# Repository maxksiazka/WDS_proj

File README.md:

# Wizualizacja kokpitu samolotu 

## O projekcie
Projekt polega na zaprojektowaniu i implementacji aplikacji graficznej mimikującej nowoczesny "szklany kokpit" samolotu.

## Warstwa sprzętowa (Embedded i Czujniki)
Projekt obejmuje warstwę embedded, w której centralną funkcję pełni mikrokontroler **Raspberry Pi Pico 2W**. Do mikrokontrolera podłączony jest zestaw następujących układów pomiarowych:
* **Moduł inercyjny (IMU 10-DoF)** - zawierający akcelerometr, żyroskop, magnetometr oraz barometr statyczny. - *modGY-86*:
  * **Akcelerometr i żyroskop**: Służą do wyznaczania sztucznego horyzontu (ang. *attitude indicator*).
  * **Magnetometr**: Umożliwia sterowanie wirtualnym kompasem (ang. *heading indicator*) oraz orientowanie wskaźnika kursu.
  * **Barometr statyczny**: Służy do przeliczania spadku ciśnienia w celu określenia wysokości lotu oraz uzyskania prędkości pionowej, pełniąc funkcję wariometru.
* **System pomiaru ciśnienia różnicowego** - *Hx-710B*: Działa jako prędkościomierz ciśnieniowy, mający na celu uzyskanie prędkości przyrządowej statku powietrznego (ang. *indicated airspeed* - IAS).
* **Moduł GPS** - *NEO-M8N*: Wykorzystywany do reprezentacji prędkości nad ziemią (ang. *ground speed* - GS) oraz rzeczywistego kąta ścieżki (ang. *course over ground* - COG).

## Architektura oprogramowania
* Architektura systemu opiera się na ciągłej akwizycji wartości z wymienionych układów pomiarowych, ich wstępnym przetwarzaniu na poziomie mikrokontrolera oraz strumieniowaniu do komputera PC.
* Algorytmy te integrują surowe odczyty, tworząc spójny, odporny na zakłócenia i responsywny interfejs łączący funkcjonalności ekranów PFD (ang. *Primary Flight Display*) oraz MFD (ang. *Multi-Function Display*).
* Intefejs będzie osobną aplikacją desktopową, która będzie odbierać dane z mikrokontrolera i wizualizować je w czasie rzeczywistym za pomocą biblioteki graficznej Qt6.

## Specyfikacja finalnego produktu
* Finalnym produktem jest zintegrowany system pomiarowo-wizualizacyjny, który ma na celu imitację samolotu.
* Część sprzętowa, mająca formę fizycznej makiety, pełni funkcję uproszczonego układu AHRS (ang. *Attitude and Heading Reference System*) zintegrowanego z czujnikiem ciśnienia różnicowego (pomiar prędkości przyrządowej) oraz odbiornikiem GPS.
* Zbierane dane są strumieniowane do aplikacji na komputerze PC, która realizuje funkcje interfejsów PFD oraz MFD.
* Gotowa aplikacja bezpośrednio reaguje na zmiany położenia makiety oraz zmiany środowiskowe. **Data**: 20 marca 2026.

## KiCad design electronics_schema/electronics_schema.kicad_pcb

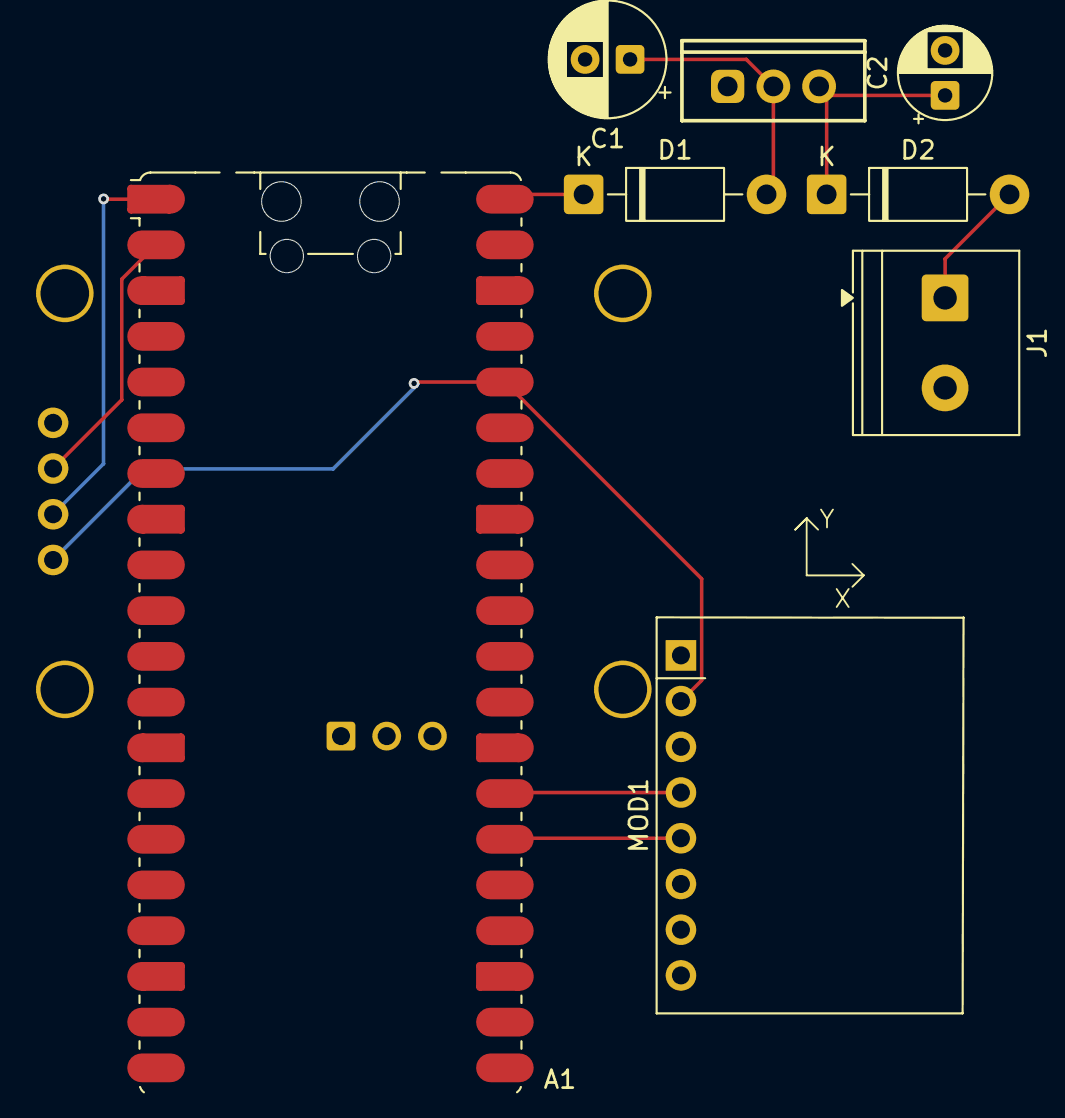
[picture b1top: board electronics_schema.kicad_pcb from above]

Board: 2 copper layers, 9 parts (1 on the bottom side), 10 nets.

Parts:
A1: RaspberryPi_Pico_W; RaspberryPi_Pico_W_SMD_HandSolder
C1: 100u; CP_Radial_D6.3mm_P2.50mm
C2: 10u; CP_Radial_D5.0mm_P2.50mm
D1, D2: 1N5819; D_DO-41_SOD81_P10.16mm_Horizontal
J1: Screw_Terminal_2_P5.00mm; TerminalBlock_Phoenix_PT-1,5-2-5.0-H_1x02_P5.00mm_Horizontal
MOD1: modGY-87
MOD2: GY-GPS6MV2
U1: LM1117T-5.0; TO-220-3

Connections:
3v3: A1.36 (3V3), MOD1.2 (3.3V), MOD2.1 (VCC)
/gps_RX: A1.1 (GPIO0), MOD2.2 (RX)
/gps_TX: A1.2 (GPIO1), MOD2.3 (TX)
/imu_SCL: A1.27 (GPIO21), MOD1.4 (SCL)
/imu_SDA: A1.26 (GPIO20), MOD1.5 (SDA)
GND: A1.3 (GND), A1.8 (GND), A1.13 (GND), A1.18 (GND), A1.23 (GND), A1.28 (GND), A1.38 (GND), C1.2, C2.2, J1.2, MOD1.3 (GND), MOD2.4 (GND), U1.1 (GND)
unnamed: A1.40 (VBUS), D1.1 (K)
unnamed: C1.1, D1.2 (A), U1.2 (VO)
unnamed: C2.1, D2.1 (K), U1.3 (VI)
VBATT: D2.2 (A), J1.1

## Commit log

2026-03-21 feat(project): Added project description to README.md, created TASKS.md with approximate to-do list
2026-03-21 feat(hardware): Created a template Pico 2W project
2026-03-21 feat(hardware): added simple hello world, gitignore
2026-03-21 feat(hardware): wrote UDP IPv4 address discovery code
2026-03-21 feat(hardware): added legacy TCP code from maxksiazka/SR_Project, needs adaptation
2026-03-23 feat(hardware): finished udp discovery protocol, changed lwip callbacks to static
2026-03-24 feat(qt): Created a simple TCP server QtCoreApplication, with UDP IP Address broadcasting.
    The application is very barebones for now, for now its purpose is to
    verify the link between the server and MCU.
    Todo:
    - Check IP and TCP port discovery
    - Add dynamic TCP port discovery on the mcu side.
2026-03-24 chore: removed mistakenly added compile_commands.json, add it to .gitignore
2026-03-24 feat(mcuemulator): created app that receives udp broadcast, and connects to specified TCP server
2026-03-24 test(qt): mcuemulator tested, connects successfully
    Next step: data recv implementation
2026-04-01 feat(electronics): added early version of electronics schema
2026-04-09 feat(libgy87): added imu library to project
2026-04-11 chore: updated submodule
2026-04-11 feat(hardware): added IMU support, updated submodule
2026-04-11 feat(hardware): successfully tested IMU module
2026-04-11 chore: move LED_PIN definition to common.h, remove extraneous printf() calls
2026-04-16 chore: corrected documentation formatting
2026-04-16 feat(hardware): successful testing of the IMU module
2026-04-16 chore: updated TASKS.md
2026-04-20 feat(desktop): add SensorLink documentation
2026-04-20 feat(hardware): Add CRC16 to imu.c, Add TCP documentation, Add UDP Documentation
2026-04-22 feat(hardware): add documentation, move schema to kicad 10
2026-04-22 feat(desktop): add documentation handling in doxygen
2026-04-22 feat(hardware): change imu_packet_t signature to const in checksum calculation
2026-04-22 feat(hardware): add doxygen support
2026-04-22 feat(hardware): add name to imu data structure
2026-05-06 feat(desktop): a most basic MainWindow implementation.
2026-05-07 feat(kalman): implement Extended Kalman Filter, omitting Yaw calculation.
2026-05-07 feat(desktop): test connection with mcu emulator, implement data transfer between SensorLink and Data fusion Engine
2026-05-07 feat(desktop): DataFusionEngine docs
2026-05-07 feat(desktop): Add @author and @date annotation to DataFusionEngine file documentation
2026-05-09 feat(desktop): add PFD class, add ArtificialHorizon class
2026-05-09 fix: broken translate on the pitch ladder
2026-05-13 feat(desktop): Added a Display Control Panel Object, Create custom QNH_knob, document everything so far
2026-05-13 feat(desktop): add placeholders for the objects to be created
2026-05-13 feat(desktop): connect DataFusion to PFD, fix bugs
2026-05-20 feat: sanity dwindling
2026-05-24 feat: first implementation of airspeed indicator
2026-05-24 feat: integrate new airspeed indicator in PFD
2026-05-24 feat: implement airspeed kalman filter
2026-05-24 docs: documented DataFusionEngine.hpp
2026-05-24 feat: increase sensor variance + successful testing of airspeed indicator
2026-05-24 docs: documented SensorLink
2026-05-24 docs: fixed doc commands
2026-05-24 feat: implement value tracking in QNHKnob
2026-05-24 feat: transfer data from QNH knob and SensorLink to get an AltitudeReading
2026-05-25 feat: implemented altimeter based on airspeed indicator
2026-05-25 fix: change gyro data to match expectations
2026-05-25 feat: implement a 2D Kalman Filter that tracks heading
2026-05-25 chore: renamed HeadingIndicator to HSI
2026-05-25 chore: rename functions to remove ambiguous or misleading names
2026-05-25 feat: implement DCP - CRS Knob and HSI
2026-05-26 fix: change vectors to match wxyz quaternion scheme, mark most of the code const
2026-05-26 feat: add SystemStatusHeader
2026-05-26 feat: add a pitch emulator, add white noise to emulators
2026-05-26 chore: remove extra comments
2026-05-26 docs: syzyf
2026-05-27 feat: remove print from tcp_sent_callback
2026-05-28 feat(hardware): add hx710 module
2026-06-02 feat(hardware): scale diff pressure sensor readings, implement airspeed calcution logic
2026-06-02 feat(desktop): Implement 4D EKF for heading
2026-06-09 chore: resize window to desktop size
2026-06-09 feat: refactor Artificial horizon, now includes width, and looks better
2026-06-09 test: add roll_sim for on-the-fly testing
2026-06-09 chore: add const specifiers
2026-06-09 chore: add const specifiers to Altimeter
2026-06-09 chore: add const markings to HSI.cpp
2026-06-09 feat: add MFD class as final block of the project
2026-06-09 feat: integrated MFD into MainWindow, removed deprecated CreatePanel function
2026-06-09 chore: renamed misleading lib to dcp_instruments
2026-06-09 chore: updated CMakeLists with new lib names
2026-06-09 chore: renamed instruments to pfd instruments
2026-06-09 feat: add empty NavigationScreen and TelemetryScreen
2026-06-09 feat(desktop): implement basic telemetry scree
2026-06-09 feat: create basic navigation screen
2026-06-09 feat: integration of Telemetry and Navigation Screens into the app.
2026-06-09 feat: delete emulators from git
2026-06-09 docs: Updated documentation for all dat
2026-06-09 feat: FPLN load integration
2026-06-09 feat: multithread DataFusion, add mainpage.dox, change binary name
2026-06-24 feat: housekeeping, adding colors to TelemetryScreen
2026-06-24 docs: Documented everything version final
2026-06-24 feat: verification of gps data
2026-06-24 docs: last change lol
2026-06-24 chore: updated gitignore
